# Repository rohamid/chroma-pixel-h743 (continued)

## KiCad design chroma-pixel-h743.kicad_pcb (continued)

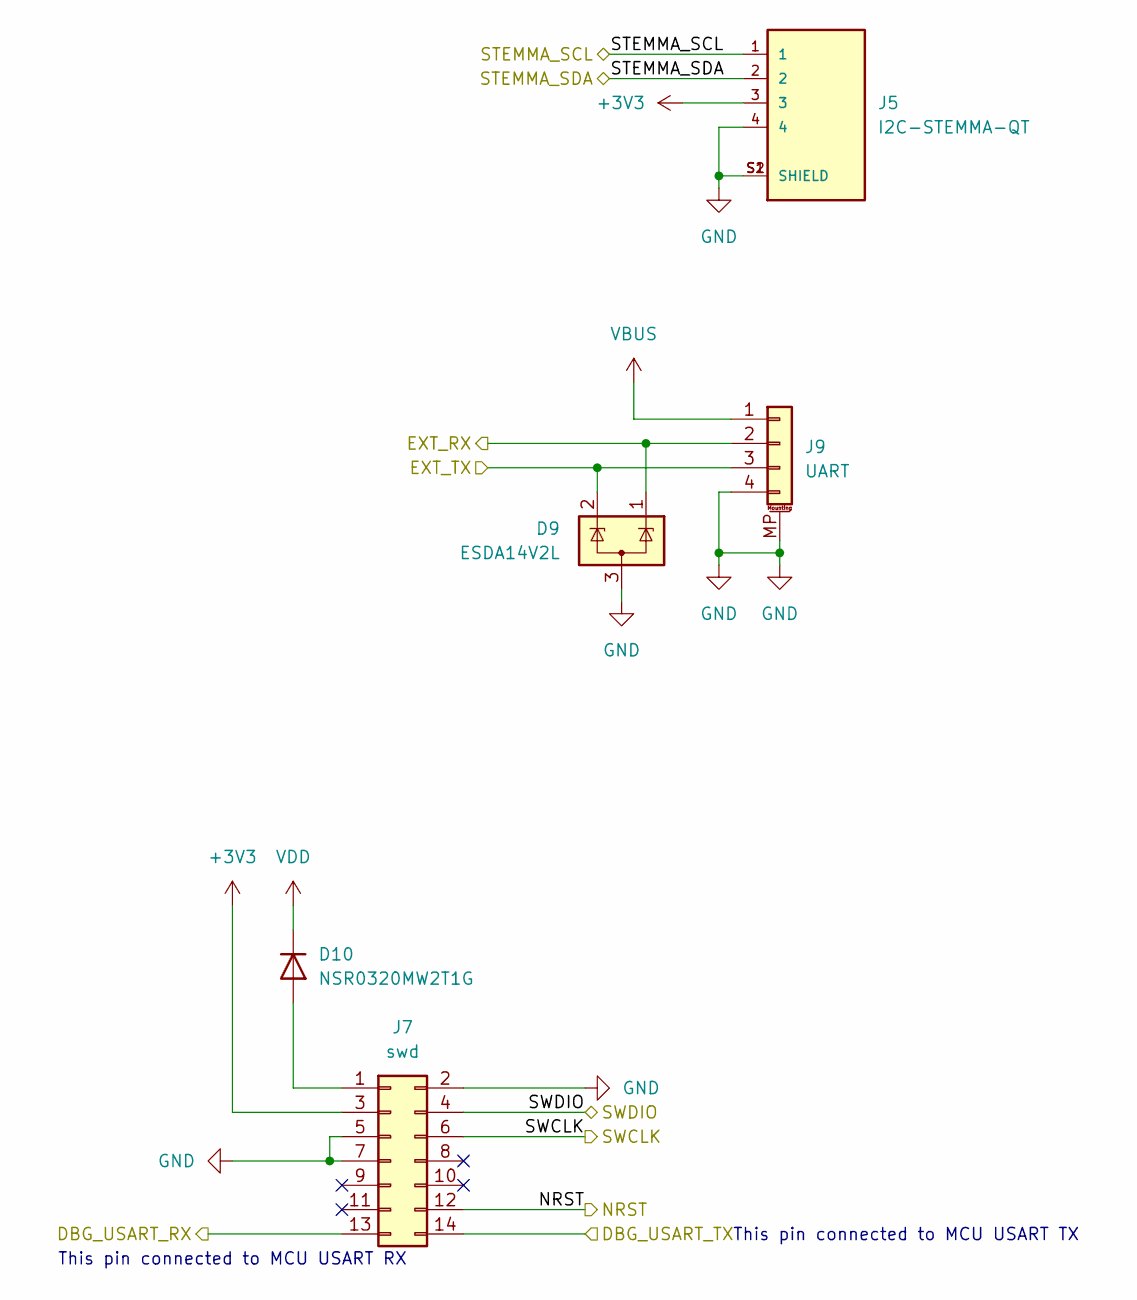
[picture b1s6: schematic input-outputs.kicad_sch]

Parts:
D9: ESDA14V2L; SOT-23; JLCPCB Part # C2682282
D10: NSR0320MW2T1G; D_SOD-323; JLCPCB Part # C48192
J5: I2C-STEMMA-QT; JST_SM04B-SRSS-TB_LF__SN_; JLCPCB Part # C160404
J7: swd; PinHeader_2x07_P1.27mm_Vertical_SMD; JLCPCB Part # C2881912
J9: UART; Hirose_DF13C_CL535-0404-8-51_1x04-1MP_P1.25mm_Vertical; JLCPCB Part # C7430470

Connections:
+3V3: J5.3, J7.3; also elsewhere on the board
/IO/DBG_USART_RX: J7.13; also elsewhere on the board
/IO/DBG_USART_TX: J7.14; also elsewhere on the board
/IO/EXT_RX: D9.1 (K), J9.2; also elsewhere on the board
/IO/EXT_TX: D9.2 (K), J9.3; also elsewhere on the board
/IO/NRST: J7.12; also elsewhere on the board
/IO/STEMMA_SCL: J5.1; also elsewhere on the board
/IO/STEMMA_SDA: J5.2; also elsewhere on the board
/IO/SWCLK: J7.6; also elsewhere on the board
/IO/SWDIO: J7.4; also elsewhere on the board
GND: D9.3 (A), J5.4, J5.S1 (SHIELD), J5.S2 (SHIELD), J7.2, J7.5, J7.7, J9.4, J9.MP (MountPin); also elsewhere on the board
unnamed: D10.2 (A), J7.1
VBUS: J9.1; also elsewhere on the board
VDD: D10.1 (K); also elsewhere on the board

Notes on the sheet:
This pin connected to MCU USART RX
This pin connected to MCU USART TX

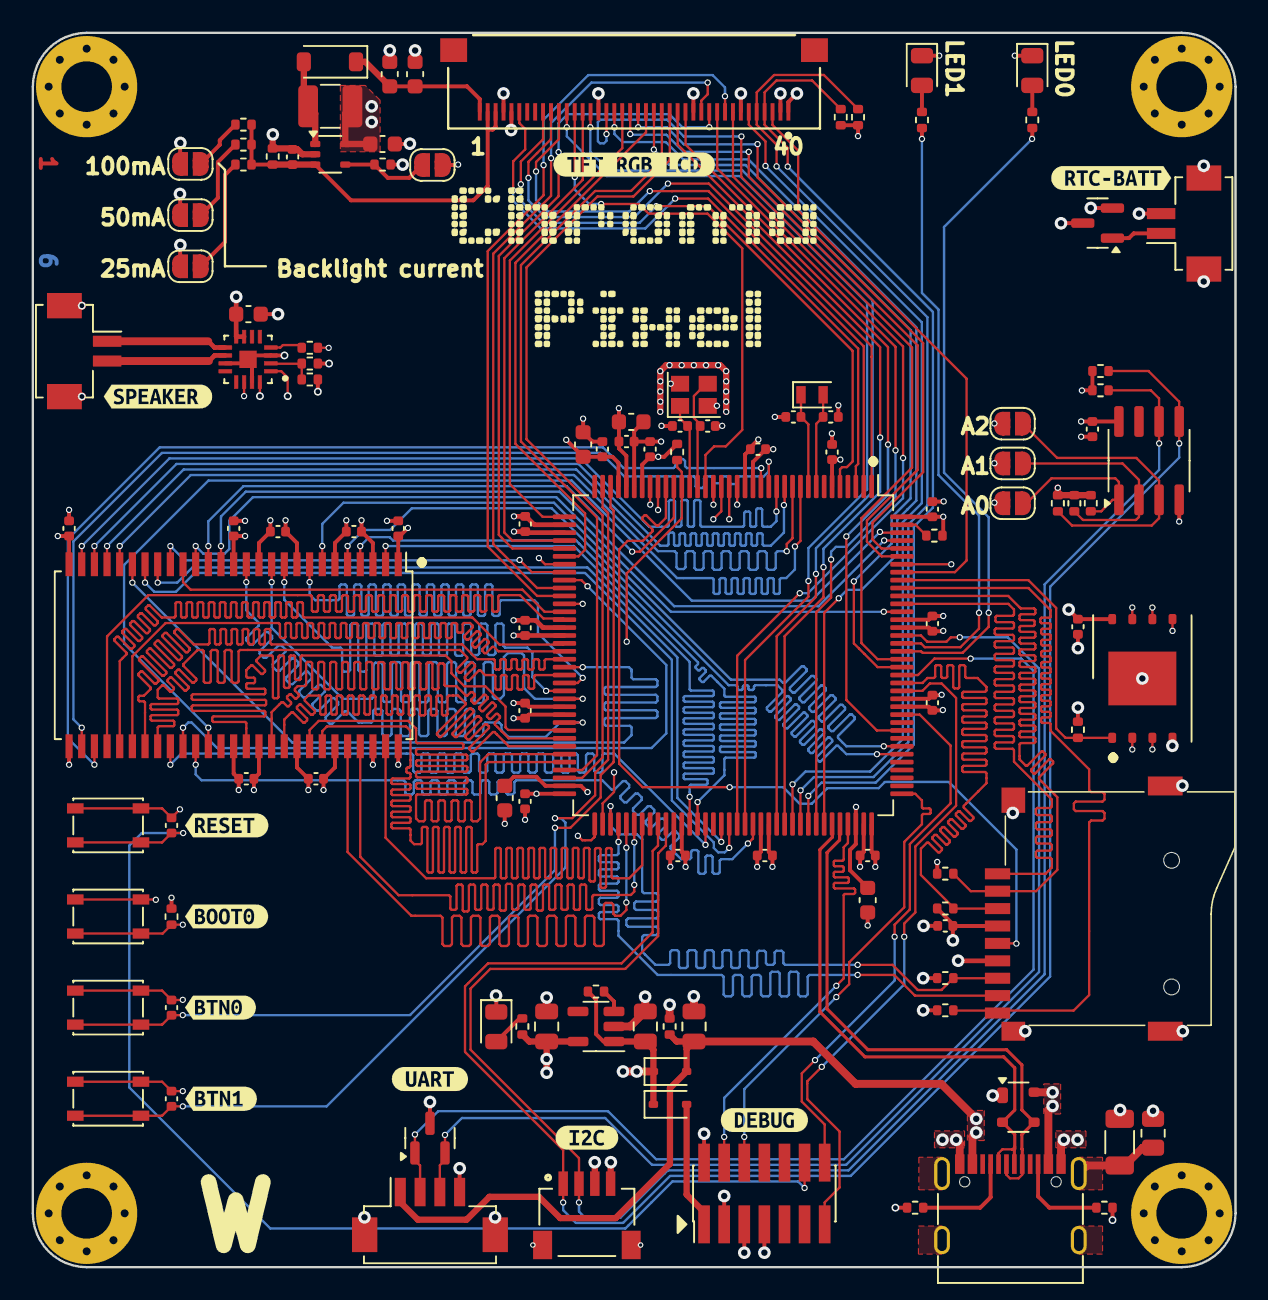
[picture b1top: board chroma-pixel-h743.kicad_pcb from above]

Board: 6 copper layers, 76.0 x 78.0 mm, 128 parts (0 on the bottom side), 135 nets.

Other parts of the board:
kibuzzard-6641D1A5: G***; kibuzzard-6641D1A5
kibuzzard-6641D1AA: G***; kibuzzard-6641D1AA
kibuzzard-6641D1B0: G***; kibuzzard-6641D1B0
kibuzzard-6641D19D: G***; kibuzzard-6641D19D
kibuzzard-6642BE6C: G***; kibuzzard-6642BE6C
kibuzzard-6642BE54: G***; kibuzzard-6642BE54
kibuzzard-6642BE85: G***; kibuzzard-6642BE85
kibuzzard-6644A0DC: G***; kibuzzard-6644A0DC
kibuzzard-66417165: G***; kibuzzard-66417165
kibuzzard-66417197: G***; kibuzzard-66417197

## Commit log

2024-07-08 LTDC route almost finished
2024-07-14 Added chroma pixel png
2024-07-15 First release H743 version
2024-07-15 Fix to small via
2025-03-18 Move to Kicad V.9. Added Pinout for CubeIDE
